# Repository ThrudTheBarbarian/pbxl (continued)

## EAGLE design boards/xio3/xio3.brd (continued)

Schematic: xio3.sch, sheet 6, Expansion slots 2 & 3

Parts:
C55, C56: 0.1uF; C0201
LD_2P, LD_3P: SML-D12D1WT86; CHIPLED_0603
R63, R64: 10K; R0201
R101, R104: 59R; R0402
SLOT2, SLOT3: PCIE_64; PCI-E_64

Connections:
!LO_CCTL!: SLOT2.A27, SLOT3.A27; also elsewhere on the board
!LO_EXTSEL!: SLOT2.A29, SLOT3.A29; also elsewhere on the board
!LO_HALT!: SLOT2.B13, SLOT3.B13; also elsewhere on the board
!LO_IRQ!: SLOT2.B14, SLOT3.B14; also elsewhere on the board
!LO_MPD!: SLOT2.A30, SLOT3.A30; also elsewhere on the board
!LO_REF!: SLOT2.B15, SLOT3.B15; also elsewhere on the board
!LO_RST!: SLOT2.B16, SLOT3.B16; also elsewhere on the board
+3V3: SLOT2.A2, SLOT3.A2, SLOT3.A3; also elsewhere on the board
+5V: C55.1, C56.1, SLOT2.B1, SLOT2.B2, SLOT2.B3, SLOT3.B1, SLOT3.B2, SLOT3.B3; also elsewhere on the board
GND: C55.2, C56.2, LD_2P.C, LD_3P.C, R63.1, R64.1, SLOT2.A1, SLOT2.A3, SLOT2.A4, SLOT2.A5, SLOT2.B32, SLOT3.A1, SLOT3.A4, SLOT3.A5, SLOT3.B32; also elsewhere on the board
HBUS0: SLOT2.B18, SLOT3.B18; also elsewhere on the board
HBUS1: SLOT2.B19, SLOT3.B19; also elsewhere on the board
HBUS2: SLOT2.B20, SLOT3.B20; also elsewhere on the board
HBUS3: SLOT2.B21, SLOT3.B21; also elsewhere on the board
HBUS4: SLOT2.B22, SLOT3.B22; also elsewhere on the board
HBUS5: SLOT2.B23, SLOT3.B23; also elsewhere on the board
HBUS6: SLOT2.B24, SLOT3.B24; also elsewhere on the board
HBUS7: SLOT2.B25, SLOT3.B25; also elsewhere on the board
HBUS8: SLOT2.B26, SLOT3.B26; also elsewhere on the board
HBUS9: SLOT2.B27, SLOT3.B27; also elsewhere on the board
HBUS10: SLOT2.B28, SLOT3.B28; also elsewhere on the board
HBUS11: SLOT2.B29, SLOT3.B29; also elsewhere on the board
HBUS12: SLOT2.B30, SLOT3.B30; also elsewhere on the board
HBUS13: SLOT2.B31, SLOT3.B31; also elsewhere on the board
LO_A0: SLOT2.A11, SLOT3.A11; also elsewhere on the board
LO_A1: SLOT2.A12, SLOT3.A12; also elsewhere on the board
LO_A2: SLOT2.A13, SLOT3.A13; also elsewhere on the board
LO_A3: SLOT2.A14, SLOT3.A14; also elsewhere on the board
LO_A4: SLOT2.A15, SLOT3.A15; also elsewhere on the board
LO_A5: SLOT2.A16, SLOT3.A16; also elsewhere on the board
LO_A6: SLOT2.A17, SLOT3.A17; also elsewhere on the board
LO_A7: SLOT2.A18, SLOT3.A18; also elsewhere on the board
LO_A8: SLOT2.A19, SLOT3.A19; also elsewhere on the board
LO_A9: SLOT2.A20, SLOT3.A20; also elsewhere on the board
LO_A10: SLOT2.A21, SLOT3.A21; also elsewhere on the board
LO_A11: SLOT2.A22, SLOT3.A22; also elsewhere on the board
LO_A12: SLOT2.A23, SLOT3.A23; also elsewhere on the board
LO_A13: SLOT2.A24, SLOT3.A24; also elsewhere on the board
LO_A14: SLOT2.A25, SLOT3.A25; also elsewhere on the board
LO_A15: SLOT2.A26, SLOT3.A26; also elsewhere on the board
LO_CLK: SLOT2.A28, SLOT3.A28; also elsewhere on the board
LO_D0: SLOT2.B5, SLOT3.B5; also elsewhere on the board
LO_D1: SLOT2.B6, SLOT3.B6; also elsewhere on the board
LO_D2: SLOT2.B7, SLOT3.B7; also elsewhere on the board
LO_D3: SLOT2.B8, SLOT3.B8; also elsewhere on the board
LO_D4: SLOT2.B9, SLOT3.B9; also elsewhere on the board
LO_D5: SLOT2.B10, SLOT3.B10; also elsewhere on the board
LO_D6: SLOT2.B11, SLOT3.B11; also elsewhere on the board
LO_D7: SLOT2.B12, SLOT3.B12; also elsewhere on the board
LO_R/!W!: SLOT2.B17, SLOT3.B17; also elsewhere on the board
LO_RD4: SLOT2.A31, SLOT3.A31; also elsewhere on the board
LO_RD5: SLOT2.A32, SLOT3.A32; also elsewhere on the board
unnamed: LD_2P.A, R101.2
unnamed: LD_3P.A, R104.2
S2_PRESENT: R63.2, R101.1, SLOT2.B4
S3_PRESENT: R64.2, R104.1, SLOT3.B4
SPI2_IRQ: SLOT2.A8; also elsewhere on the board
SPI2_MISO: SLOT2.A10; also elsewhere on the board
SPI2_MOSI: SLOT2.A9; also elsewhere on the board
SPI3_IRQ: SLOT3.A8; also elsewhere on the board
SPI3_MISO: SLOT3.A10; also elsewhere on the board
SPI3_MOSI: SLOT3.A9; also elsewhere on the board
VALID_RD: SLOT2.A7, SLOT3.A7; also elsewhere on the board
VALID_WR: SLOT2.A6, SLOT3.A6; also elsewhere on the board

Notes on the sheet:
Slots 2,3
Slot id: 0,1,0
Slot id: 0,1,1
B1,2,3 B4 A1,2,3 A4,5,6,7
+5V Card-present Slot ID GND
Orange LED

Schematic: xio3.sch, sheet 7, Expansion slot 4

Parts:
C81: 0.1uF; C0201
LD_4P: SML-D12D1WT86; CHIPLED_0603
R65: 10K; R0201
R107: 59R; R0402
SLOT4: PCIE_64; PCI-E_64

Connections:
!LO_CCTL!: SLOT4.A27; also elsewhere on the board
!LO_EXTSEL!: SLOT4.A29; also elsewhere on the board
!LO_HALT!: SLOT4.B13; also elsewhere on the board
!LO_IRQ!: SLOT4.B14; also elsewhere on the board
!LO_MPD!: SLOT4.A30; also elsewhere on the board
!LO_REF!: SLOT4.B15; also elsewhere on the board
!LO_RST!: SLOT4.B16; also elsewhere on the board
+3V3: SLOT4.A1; also elsewhere on the board
+5V: C81.1, SLOT4.B1, SLOT4.B2, SLOT4.B3; also elsewhere on the board
GND: C81.2, LD_4P.C, R65.1, SLOT4.A2, SLOT4.A3, SLOT4.A4, SLOT4.A5, SLOT4.B32; also elsewhere on the board
HBUS0: SLOT4.B18; also elsewhere on the board
HBUS1: SLOT4.B19; also elsewhere on the board
HBUS2: SLOT4.B20; also elsewhere on the board
HBUS3: SLOT4.B21; also elsewhere on the board
HBUS4: SLOT4.B22; also elsewhere on the board
HBUS5: SLOT4.B23; also elsewhere on the board
HBUS6: SLOT4.B24; also elsewhere on the board
HBUS7: SLOT4.B25; also elsewhere on the board
HBUS8: SLOT4.B26; also elsewhere on the board
HBUS9: SLOT4.B27; also elsewhere on the board
HBUS10: SLOT4.B28; also elsewhere on the board
HBUS11: SLOT4.B29; also elsewhere on the board
HBUS12: SLOT4.B30; also elsewhere on the board
HBUS13: SLOT4.B31; also elsewhere on the board
LO_A0: SLOT4.A11; also elsewhere on the board
LO_A1: SLOT4.A12; also elsewhere on the board
LO_A2: SLOT4.A13; also elsewhere on the board
LO_A3: SLOT4.A14; also elsewhere on the board
LO_A4: SLOT4.A15; also elsewhere on the board
LO_A5: SLOT4.A16; also elsewhere on the board
LO_A6: SLOT4.A17; also elsewhere on the board
LO_A7: SLOT4.A18; also elsewhere on the board
LO_A8: SLOT4.A19; also elsewhere on the board
LO_A9: SLOT4.A20; also elsewhere on the board
LO_A10: SLOT4.A21; also elsewhere on the board
LO_A11: SLOT4.A22; also elsewhere on the board
LO_A12: SLOT4.A23; also elsewhere on the board
LO_A13: SLOT4.A24; also elsewhere on the board
LO_A14: SLOT4.A25; also elsewhere on the board
LO_A15: SLOT4.A26; also elsewhere on the board
LO_CLK: SLOT4.A28; also elsewhere on the board
LO_D0: SLOT4.B5; also elsewhere on the board
LO_D1: SLOT4.B6; also elsewhere on the board
LO_D2: SLOT4.B7; also elsewhere on the board
LO_D3: SLOT4.B8; also elsewhere on the board
LO_D4: SLOT4.B9; also elsewhere on the board
LO_D5: SLOT4.B10; also elsewhere on the board
LO_D6: SLOT4.B11; also elsewhere on the board
LO_D7: SLOT4.B12; also elsewhere on the board
LO_R/!W!: SLOT4.B17; also elsewhere on the board
LO_RD4: SLOT4.A31; also elsewhere on the board
LO_RD5: SLOT4.A32; also elsewhere on the board
unnamed: LD_4P.A, R107.2
S4_PRESENT: R65.2, R107.1, SLOT4.B4
SPI4_IRQ: SLOT4.A8; also elsewhere on the board
SPI4_MISO: SLOT4.A10; also elsewhere on the board
SPI4_MOSI: SLOT4.A9; also elsewhere on the board
VALID_RD: SLOT4.A7; also elsewhere on the board
VALID_WR: SLOT4.A6; also elsewhere on the board

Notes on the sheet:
Slot 4
B1,2,3 B5,6,7 B4 A1,2,3 A4,5,6,7
+5V Slot 3.3v Card-present Slot ID GND
Orange LED

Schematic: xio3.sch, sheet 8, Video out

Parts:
JP2: PINHD-2X10; 2X10
R28, R29: 100R; R0201
RN1, RN5, RN8: 1K; ACAS0612
RN2, RN3, RN4, RN6, RN7, RN9, RN10, RN11: 2K; ACAS0612
U$2: DB15

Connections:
+5V: JP2.2; also elsewhere on the board
GND: JP2.20, U$2.5, U$2.6, U$2.7, U$2.8, U$2.10; also elsewhere on the board
unnamed: RN4.2A (1), RN4.3A (1)
unnamed: RN2.3B (2), RN2.4B (2)
unnamed: RN3.1B (2), RN3.2B (2)
unnamed: RN3.2A (1), RN3.3A (1)
unnamed: RN3.3B (2), RN3.4B (2)
unnamed: RN6.3B (2), RN6.4B (2)
unnamed: RN7.1B (2), RN7.2B (2)
unnamed: RN7.2A (1), RN7.3A (1)
unnamed: RN7.3B (2), RN7.4B (2)
unnamed: RN4.1B (2), RN4.2B (2)
unnamed: RN4.3B (2), RN4.4B (2)
unnamed: RN4.4A (1), RN11.1A (1)
unnamed: RN11.1B (2), RN11.2B (2)
unnamed: RN11.2A (1), RN11.3A (1)
unnamed: RN11.3B (2), RN11.4B (2)
unnamed: RN9.3B (2), RN9.4B (2)
unnamed: RN10.1B (2), RN10.2B (2)
unnamed: RN10.2A (1), RN10.3A (1)
unnamed: RN10.3B (2), RN10.4B (2)
VGA_B0: JP2.1, RN10.1A (1); also elsewhere on the board
VGA_B1: JP2.3, RN9.3A (1); also elsewhere on the board
VGA_B2: JP2.5, RN9.1A (1); also elsewhere on the board
VGA_B3: JP2.7, RN8.4A (1); also elsewhere on the board
VGA_B4: JP2.9, RN8.1A (1), RN8.2A (1); also elsewhere on the board
VGA_BLU: RN8.1B (2), RN8.2B (2), RN8.4B (2), RN9.1B (2), RN9.4A (1), RN10.4A (1), U$2.3
VGA_G0: JP2.4, RN4.1A (1); also elsewhere on the board
VGA_G1: JP2.6, RN7.1A (1); also elsewhere on the board
VGA_G2: JP2.8, RN6.3A (1); also elsewhere on the board
VGA_G3: JP2.10, RN6.1A (1); also elsewhere on the board
VGA_G4: JP2.12, RN5.4A (1); also elsewhere on the board
VGA_G5: JP2.14, RN5.1A (1), RN5.2A (1); also elsewhere on the board
VGA_GRN: RN5.1B (2), RN5.2B (2), RN5.4B (2), RN6.1B (2), RN6.4A (1), RN7.4A (1), RN11.4A (1), U$2.2
VGA_HS: R29.1, U$2.13
VGA_HSYNC: JP2.16, R29.2; also elsewhere on the board
VGA_R0: JP2.11, RN3.1A (1); also elsewhere on the board
VGA_R1: JP2.13, RN2.3A (1); also elsewhere on the board
VGA_R2: JP2.15, RN2.1A (1); also elsewhere on the board
VGA_R3: JP2.17, RN1.4A (1); also elsewhere on the board
VGA_R4: JP2.19, RN1.1A (1), RN1.2A (1); also elsewhere on the board
VGA_RED: RN1.1B (2), RN1.2B (2), RN1.4B (2), RN2.1B (2), RN2.4A (1), RN3.4A (1), U$2.1
VGA_VS: R28.1, U$2.14
VGA_VSYNC: JP2.18, R28.2; also elsewhere on the board

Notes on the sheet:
Video Out

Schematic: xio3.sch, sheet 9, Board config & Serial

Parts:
ARCH_ID: 209-4MS; EDG-04
C89, C90, C91, C92, C94: 0.1uF; C0201
MEM_ID: 209-2MS; EDG-02
PID: 209-3MS; EDG-03
R6, R7, R8, R9, R14, R15, R16, R17, R18: 47K; R0201
R11, R12, R122, R123, R124: 1K; R0201
SERIAL0: 9-way D; DB9
SERIAL_BUF0: MAX3232ECDR; SO16

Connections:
+3V3: C94.2, R11.1, R12.1, R122.1, R123.1, R124.1, SERIAL_BUF0.16 (VCC); also elsewhere on the board
ARCH0: ARCH_ID.1, R9.1
ARCH1: ARCH_ID.2, R8.1
ARCH2: ARCH_ID.3, R7.1
ARCH3: ARCH_ID.4, R6.1
CTS1: SERIAL0.7, SERIAL_BUF0.8 (R2IN)
GND: C91.2, C92.2, C94.1, R6.2, R7.2, R8.2, R9.2, R14.2, R15.2, R16.2, R17.2, R18.2, SERIAL0.5, SERIAL_BUF0.15 (GND); also elsewhere on the board
MCU_CTS: SERIAL_BUF0.9 (R2OUT); also elsewhere on the board
MCU_RTS: R12.2, SERIAL_BUF0.10 (T2IN); also elsewhere on the board
MCU_RX: SERIAL_BUF0.12 (R1OUT); also elsewhere on the board
MCU_TX: R11.2, SERIAL_BUF0.11 (T1IN); also elsewhere on the board
MEM0: MEM_ID.1, R18.1
MEM1: MEM_ID.2, R17.1
unnamed: ARCH_ID.5, ARCH_ID.6, ARCH_ID.7, ARCH_ID.8, R122.2
unnamed: C89.2, SERIAL_BUF0.1 (C1+)
unnamed: C89.1, SERIAL_BUF0.3 (C1-)
unnamed: C90.2, SERIAL_BUF0.4 (C2+)
unnamed: C90.1, SERIAL_BUF0.5 (C2-)
unnamed: C91.1, SERIAL_BUF0.6 (V-)
unnamed: C92.1, SERIAL_BUF0.2 (V+)
unnamed: MEM_ID.3, MEM_ID.4, R123.2
unnamed: PID.4, PID.5, PID.6, R124.2
PID0: PID.1, R16.1
PID1: PID.2, R15.1
PID2: PID.3, R14.1
RTS1: SERIAL0.8, SERIAL_BUF0.7 (T2OUT)
RX1: SERIAL0.3, SERIAL_BUF0.13 (R1IN)
TX1: SERIAL0.2, SERIAL_BUF0.14 (T1OUT)

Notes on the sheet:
Architecture selection
Peripheral-ID selection
Memory-emulation selection
Serial & Config
Board Config
2-way and 4-way DIPs not at Seeed
For Vcc=3.3v, all caps are 0.1uF (See Table 2, pg 9 in datasheet)
the 'E' designation on the MAX3232 indicates that it has ESD protection built in
Serial I/O

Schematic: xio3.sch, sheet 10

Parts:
C41: 22uF; C0805
C42: 1uF; C0201
C43: 10uF; C0402K
C134: 0.1uF; C0201
R36, R37, R38, R39, R40, R41: 4K7; R0402
SD_SLOT: 5025700893

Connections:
+3V3: C41.1, C42.1, C43.1, C134.2, R36.2, R37.2, R38.2, R39.2, R40.2, R41.2, SD_SLOT.P$4 (VDD); also elsewhere on the board
GND: C41.2, C42.2, C43.2, C134.1, SD_SLOT.GND0 (SH1), SD_SLOT.GND1 (SH2), SD_SLOT.GND2 (SH3), SD_SLOT.GND3 (SH4), SD_SLOT.GND4 (SH5), SD_SLOT.P$6 (VSS); also elsewhere on the board
SD0: R36.1, SD_SLOT.P$7 (DAT0); also elsewhere on the board
SD1: R37.1, SD_SLOT.P$8 (DAT1); also elsewhere on the board
SD2: R38.1, SD_SLOT.P$1 (DAT2); also elsewhere on the board
SD3: R39.1, SD_SLOT.P$2 (DAT3); also elsewhere on the board
SDCD: R41.1, SD_SLOT.DTCT (CD); also elsewhere on the board
SDCLK: SD_SLOT.P$5 (CLK); also elsewhere on the board
SDCMD: R40.1, SD_SLOT.P$3 (CMD); also elsewhere on the board

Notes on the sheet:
Place pull-ups close to card socket
SD Card

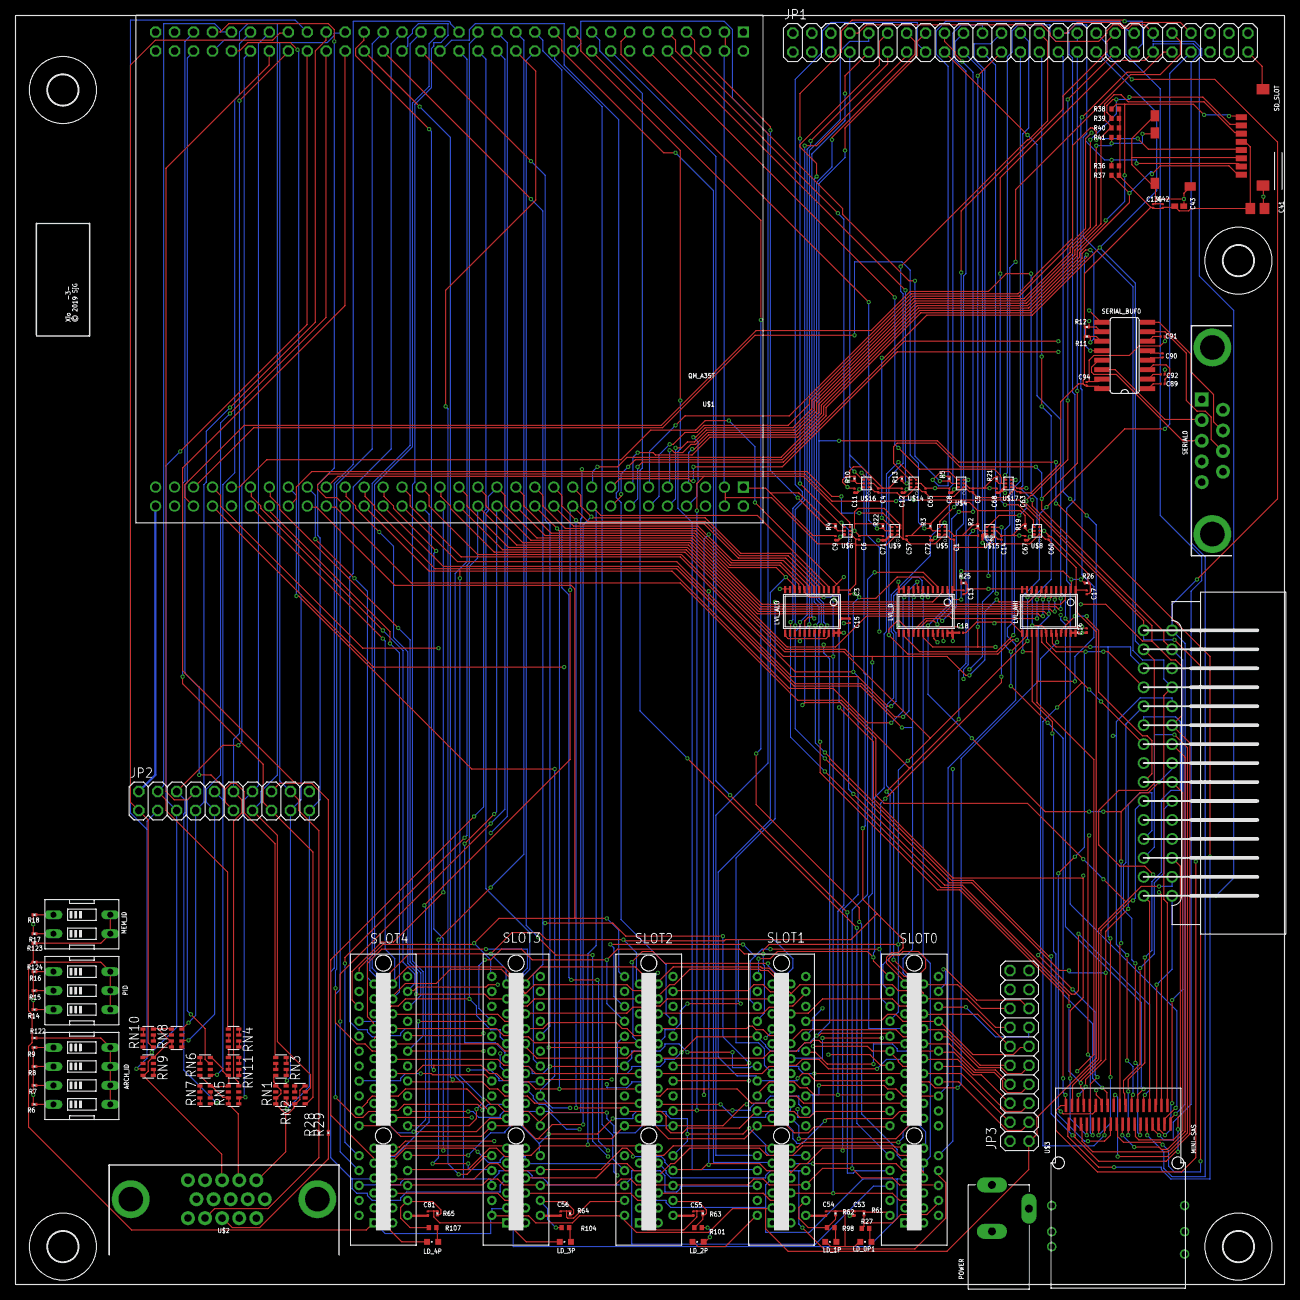
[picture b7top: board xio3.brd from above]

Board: 4 copper layers, 170.0 x 170.0 mm, 132 parts (0 on the bottom side), 201 nets.

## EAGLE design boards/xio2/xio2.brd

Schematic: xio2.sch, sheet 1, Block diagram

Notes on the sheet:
USB-C
STM32H743 (XIO) (TFBGA 240+25)
SPI4
@100 MHz
Slots 0..4
Bus Signals. Generate !D1xx!, !CCTL!, !S4!, !S5! from address. Total is 38 signals
RS232
32 MB SDRAM
/41
(32 bit)
POWER SW
USB Full-speed
CURRENT_OVER
VBUS_ENABLE
SD Card
@48
@400
NCP380
(OTG mode)
USB 'A'
DB9
5v supply @ 10A - Total power supply is 50W 3.3v from 5V, max power provided= 10A 3.3v main-board current sinks (max, in mA)
'XIO' STM32H7 IS66WV51216EBLL MAX3232 LEDs x6 NCP380 FPGA Slots Total
750 25 2 20 1 2000 5000 7798
0.5 mm core
0.12mm pre-preg
0.035mm
0.017mm
Layer stack-up
GND
Power
Dielectric constant: 4.2
Cycle time = 558ns
Valid address
Write
Read
177ns
422ns
486ns
225ns

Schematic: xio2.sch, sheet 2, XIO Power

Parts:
C1, C34: 10uF; C0402K
C2, C3, C4, C5, C6, C7, C8, C9, C10, C13, C16, C26, C27, C28, C29, C31, C32, C33, C98: 0.1uF; C0201
C14, C15: 16pF; C0201
C17, C18, C99: 2.2uF; C0201
H1, H2, H4, H5: MOUNT-HOLE3.2; 3,2
POWER: dc5vin; DCJ3P-14.2X11.0X9.0MM
R1, R5, R53, R72: 0R; R0201
R21: 33R; R0201
R88, R89, R90: 10K; R0201
XIO: STM32H743-XIO; BGA289C80P17X17_1400X1400X110
XIO-SWD: XIO_JTAG; SWD_DEBUG
Y2: FA-238 25.0000MB-K3; CRYSTAL_3.2X2.5

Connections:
!RESET!: C98.1, R89.2, XIO.K1 (!RST!), XIO-SWD.P10 (RESET); also elsewhere on the board
+3V3: C2.1, C3.1, C4.1, C5.1, C6.1, C7.1, C8.1, C9.1, C10.1, C16.1, C26.1, C27.1, C28.1, C29.1, C31.1, C32.1, C33.1, C34.1, R5.1, R21.2, R53.1, R88.1, R89.1, R90.1, XIO.A6 (VDDLDO), XIO.B1 (VBAT), XIO.C17 (VDDLDO), XIO.E6 (VDD), XIO.E9 (VDD), XIO.E11 (VDD), XIO.F5 (VDD), XIO.F17 (VDD33USB), XIO.G5 (VDD), XIO.G13 (VDD), XIO.H5 (VDD), XIO.H13 (VDD), XIO.J13 (VDD), XIO.K5 (VDD), XIO.K13 (VDD), XIO.L5 (VDD), XIO.L13 (VDD), XIO.M5 (VDD), XIO.M13 (VDD), XIO.N7 (VDD), XIO.N8 (VDD), XIO.N10 (VDD), XIO.N11 (VDD), XIO.N12 (VDD), XIO.P17 (VDD), XIO.U12 (VDDLDO), XIO-SWD.P1 (VDD_OUT); also elsewhere on the board
+5V: POWER.+; also elsewhere on the board
AGND: C1.2, C13.2, R72.2, XIO.N1 (VREF-), XIO.P1 (VSSA)
BOOT0: R1.1, R5.2, XIO.E8 (BOOT0)
GND: C2.2, C3.2, C4.2, C5.2, C6.2, C7.2, C8.2, C9.2, C10.2, C14.2, C15.2, C16.2, C17.2, C18.2, C26.2, C27.2, C28.2, C29.2, C31.2, C32.2, C33.2, C34.2, C98.2, C99.2, POWER.-1 (-), R1.2, R72.1, XIO.A1 (VSS), XIO.A17 (VSS), XIO.B2 (VSS), XIO.B6 (VSS), XIO.C10 (VSS), XIO.C13 (VSS), XIO.C16 (VSS), XIO.G7 (VSS), XIO.G8 (VSS), XIO.G9 (VSS), XIO.G10 (VSS), XIO.G11 (VSS), XIO.G16 (VSS), XIO.H7 (VSS), XIO.H8 (VSS), XIO.H9 (VSS), XIO.H10 (VSS), XIO.H11 (VSS), XIO.J3 (VSS), XIO.J7 (VSS), XIO.J8 (VSS), XIO.J9 (VSS), XIO.J10 (VSS), XIO.J11 (VSS), XIO.J16 (VSS), XIO.J17 (VSS), XIO.K7 (VSS), XIO.K8 (VSS), XIO.K9 (VSS), XIO.K10 (VSS), XIO.K11 (VSS), XIO.K15 (VSS), XIO.L7 (VSS), XIO.L8 (VSS), XIO.L9 (VSS), XIO.L10 (VSS), XIO.L11 (VSS), XIO.L15 (VSS), XIO.M15 (VSS), XIO.N16 (VSS), XIO.R4 (VSS), XIO.R8 (VSS), XIO.T12 (VSS), XIO.U1 (VSS), XIO.U17 (VSS), XIO-SWD.P3 (GND), XIO-SWD.P5 (GND), XIO-SWD.P9 (GND); also elsewhere on the board
PDR_ON: R53.2, XIO.E7 (PDR_ON)
XIO_CLK_IN: C14.1, XIO.J1 (PH0), Y2.2
XIO_CLK_OUT: C15.1, XIO.J2 (PH1), Y2.1
XIO_RX: XIO.F13 (PC7), XIO-SWD.P8 (USART_RX)
XIO_SWDCLK: XIO.B14 (PA14), XIO-SWD.P4 (SWD_CLK)
XIO_SWDIO: R90.2, XIO.C15 (PA13), XIO-SWD.P2 (SWDIO)
XIO_TX: R88.2, XIO.F14 (PC6), XIO-SWD.P6 (USART_TX)
XIO_VCAP1: C18.1, XIO.U11 (VCAP1)
XIO_VCAP2: C17.1, XIO.D17 (VCAP2)
XIO_VCAP3: C99.1, XIO.A7 (VCAP3)
XIO_VDDA: C1.1, C13.1, R21.1, XIO.L1 (VDDA), XIO.M1 (VREF+)

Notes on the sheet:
Power entry
XIO POWER
Regulated 5v supply at 10A. (JYH05010000B) Partial power plane on layer 14
Caps placed close to VDDA pin
Caps placed close to VCAP pins
(Load Cap 10pF, stray Cap 2pF)
Pullups
Filter on VDDA
Pullups etc. in panel to left
C.res1 = C.res2 = 2(C.load - C.stray)
5v-in is ok to NC

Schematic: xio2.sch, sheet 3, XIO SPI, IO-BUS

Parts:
R26, R27, R91, R92, R93: 33R; R0201
SPI_DBG: PINHD-1X5; 1X05
XIO: STM32H743-XIO; BGA289C80P17X17_1400X1400X110
XSPI5_DBG, XSPI6_DBG: PINHD-1X3; 1X03

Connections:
!ADDR_VALID_READ!: XIO.M2 (PC1); also elsewhere on the board
!ADDR_VALID_WRITE!: XIO.M3 (PC2); also elsewhere on the board
!IO_EXP_IRQ!: XIO.D3 (PE3); also elsewhere on the board
!IO_EXP_SEL!: XIO.N2 (PH2); also elsewhere on the board
!SPI_IRQ!: XIO.D2 (PE4); also elsewhere on the board
HOST_A0: XIO.U5 (PB0); also elsewhere on the board
HOST_A1: XIO.T5 (PB1); also elsewhere on the board
HOST_A2: XIO.R6 (PB2); also elsewhere on the board
HOST_A3: XIO.C6 (PB3); also elsewhere on the board
HOST_A4: XIO.B7 (PB4); also elsewhere on the board
HOST_A5: XIO.A5 (PB5); also elsewhere on the board
HOST_A6: XIO.B5 (PB6); also elsewhere on the board
HOST_A7: XIO.C5 (PB7); also elsewhere on the board
HOST_A8: XIO.D5 (PB8); also elsewhere on the board
HOST_A9: XIO.D4 (PB9); also elsewhere on the board
HOST_A10: XIO.P11 (PB10); also elsewhere on the board
HOST_A11: XIO.P12 (PB11); also elsewhere on the board
HOST_A12: XIO.T14 (PB12); also elsewhere on the board
HOST_A13: XIO.U14 (PB13); also elsewhere on the board
HOST_A14: XIO.U15 (PB14); also elsewhere on the board
HOST_A15: XIO.T15 (PB15); also elsewhere on the board
unnamed: R26.2, XIO.C3 (PE2)
unnamed: R27.2, XIO.E5 (PE6)
SPI_CLK: R26.1, SPI_DBG.1; also elsewhere on the board
SPI_IRQ0: SPI_DBG.4, XIO.H15 (PG3); also elsewhere on the board
SPI_IRQ1: XIO.G15 (PG6); also elsewhere on the board
SPI_IRQ2: XIO.A10 (PG9); also elsewhere on the board
SPI_IRQ3: XIO.A9 (PG10); also elsewhere on the board
SPI_IRQ4: XIO.B9 (PG11); also elsewhere on the board
SPI_MISO: SPI_DBG.2, XIO.D1 (PE5); also elsewhere on the board
SPI_MOSI: R27.1, SPI_DBG.3; also elsewhere on the board
SPI_MUX_IN: XIO.P2 (PH3); also elsewhere on the board
SPI_SS0: SPI_DBG.5, XIO.L2 (PC0); also elsewhere on the board
SPI_SS1: XIO.T4 (PC4); also elsewhere on the board
SPI_SS2: XIO.U4 (PC5); also elsewhere on the board
SPI_SS3: XIO.C2 (PC14); also elsewhere on the board
SPI_SS4: XIO.C1 (PC15); also elsewhere on the board
STM_MUX_CTL: XIO.M4 (PC3); also elsewhere on the board
STM_MUX_D0: XIO.N5 (PA0); also elsewhere on the board
STM_MUX_D1: XIO.N4 (PA1); also elsewhere on the board
STM_MUX_D2: XIO.N3 (PA2); also elsewhere on the board
STM_MUX_D3: XIO.U2 (PA3); also elsewhere on the board
STM_MUX_D4: XIO.U3 (PA4); also elsewhere on the board
STM_MUX_D5: XIO.T3 (PA5); also elsewhere on the board
STM_MUX_D6: XIO.R3 (PA6); also elsewhere on the board
STM_MUX_D7: XIO.R5 (PA7); also elsewhere on the board
XSPI5_MISO: R91.2, XSPI5_DBG.2; also elsewhere on the board
XSPI5_MISO_R: R91.1, XIO.K4 (PF8)
XSPI5_MOSI: XIO.L4 (PF9), XSPI5_DBG.3; also elsewhere on the board
XSPI5_SCK: XIO.K3 (PF7), XSPI5_DBG.1; also elsewhere on the board
XSPI6_MISO: XIO.C9 (PG12), XSPI6_DBG.2; also elsewhere on the board
XSPI6_MOSI: R93.2, XSPI6_DBG.3; also elsewhere on the board
XSPI6_MOSI_R: R93.1, XIO.D8 (PG14)
XSPI6_SCK: R92.2, XSPI6_DBG.1; also elsewhere on the board
XSPI6_SCK_R: R92.1, XIO.D9 (PG13)

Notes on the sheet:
Slot SPI, @ 100MHz
XIO SPI, IOBUS
Add termination resistors close to source
SPI5 to be used with FPGA as master. SPI6 to be used with STM as master Resistors sited close to source signal
FPGA SPI, @ 100MHz
FPGA to STM32 Host interface
SPI termination
FPGA decodes bus and handles timings. Sends IRQ when bus is valid to read/write

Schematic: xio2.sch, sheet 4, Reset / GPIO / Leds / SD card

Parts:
C41: 22uF; C0805
C42: 1uF; C0201
C43: 10uF; C0402K
C134, C137: 0.1uF; C0201
C135: 120pF; C0201
C136: 0.01uF; C0201
DBG0, DBG1, DBG2: YELLOW_LED; CHIPLED_0603
R2, R3, R4: 130R; R0402
R36, R37, R38, R39, R40, R41: 47K; R0402
RESET_XIO: TAC_SWITCH; TACTILE-PTH
SD_SLOT: 5025700893
VREG_MON: TPS3808G33DBVR; SOT23-6
XIO: STM32H743-XIO; BGA289C80P17X17_1400X1400X110

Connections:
!MR!: C136.1, RESET_XIO.1, RESET_XIO.2, VREG_MON.3 (!MR!)
!RESET!: VREG_MON.1 (!RESET!); also elsewhere on the board
+3V3: C41.1, C42.1, C43.1, C134.2, C137.1, R2.1, R3.1, R4.1, R36.2, R37.2, R38.2, R39.2, R40.2, R41.2, SD_SLOT.P$4 (VDD), VREG_MON.5 (SENSE), VREG_MON.6 (VDD); also elsewhere on the board
GND: C41.2, C42.2, C43.2, C134.1, C135.2, C136.2, C137.2, RESET_XIO.3, RESET_XIO.4, SD_SLOT.GND0 (SH1), SD_SLOT.GND1 (SH2), SD_SLOT.GND2 (SH3), SD_SLOT.GND3 (SH4), SD_SLOT.GND4 (SH5), SD_SLOT.P$6 (VSS), VREG_MON.2 (GND); also elsewhere on the board
unnamed: DBG0.A, R2.2
unnamed: DBG0.C, XIO.R15 (PD11)
unnamed: DBG1.C, XIO.R16 (PD12)
unnamed: DBG2.C, XIO.R17 (PD13)
unnamed: DBG1.A, R3.2
unnamed: DBG2.A, R4.2
unnamed: C135.1, VREG_MON.4 (CT)
SD0: R36.1, SD_SLOT.P$7 (DAT0), XIO.E13 (PC8)
SD1: R37.1, SD_SLOT.P$8 (DAT1), XIO.E14 (PC9)
SD2: R38.1, SD_SLOT.P$1 (DAT2), XIO.A13 (PC10)
SD3: R39.1, SD_SLOT.P$2 (DAT3), XIO.B13 (PC11)
SDCD: R41.1, SD_SLOT.DTCT (CD), XIO.E3 (PC13)
SDCLK: SD_SLOT.P$5 (CLK), XIO.C12
SDCMD: R40.1, SD_SLOT.P$3 (CMD), XIO.D12 (PD2)

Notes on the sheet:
Debug LEDs
Unused pins
Reset, LEDs, SD, unused
Reset monitor
!MR! has internal pull-up to VDD
SD Card
Place pull-ups close to card socket
Vf = 2.1v, current = 9mA using 130R

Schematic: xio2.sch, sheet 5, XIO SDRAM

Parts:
C19, C20, C21, C22, C23, C24, C167, C168, C169, C170, C171, C172: 0.1uF; C0201
C177: 4.7uF; C0201
R120, R121: 10K; R0201
SDRAM: IS42S32160F-7TLI; SOP50P1176X120-86
XIO: STM32H743-XIO; BGA289C80P17X17_1400X1400X110

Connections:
!SDRAM_CAS!: SDRAM.18 (!CAS!), XIO.D6 (PG15)
!SDRAM_RAS!: SDRAM.19 (!RAS!), XIO.T7 (PF11)
!SDRAM_WE!: SDRAM.17 (!WE!), XIO.P4 (PH5)
+3V3: C19.1, C20.1, C21.1, C22.1, C23.1, C24.1, C167.1, C168.1, C169.1, C170.1, C171.1, C172.1, C177.1, R121.1, SDRAM.1 (VDD), SDRAM.3 (VDDQ), SDRAM.9 (VDDQ), SDRAM.15 (VDD), SDRAM.29 (VDD), SDRAM.35 (VDDQ), SDRAM.41 (VDDQ), SDRAM.43 (VDD), SDRAM.49 (VDDQ), SDRAM.55 (VDDQ), SDRAM.75 (VDDQ), SDRAM.81 (VDDQ); also elsewhere on the board
GND: C19.2, C20.2, C21.2, C22.2, C23.2, C24.2, C167.2, C168.2, C169.2, C170.2, C171.2, C172.2, C177.2, R120.2, SDRAM.6 (VSSQ), SDRAM.12 (VSSQ), SDRAM.32 (VSSQ), SDRAM.38 (VSSQ), SDRAM.44 (VSS), SDRAM.46 (VSSQ), SDRAM.52 (VSSQ), SDRAM.58 (VSS), SDRAM.72 (VSS), SDRAM.78 (VSSQ), SDRAM.84 (VSSQ), SDRAM.86 (VSS); also elsewhere on the board
unnamed: R121.2, SDRAM.67 (CKE)
unnamed: R120.1, SDRAM.20 (!CS!)
SDRAM_A0: SDRAM.25 (A0), XIO.G4 (PF0)
SDRAM_A1: SDRAM.26 (A1), XIO.G3 (PF1)
SDRAM_A2: SDRAM.27 (A2), XIO.G1 (PF2)
SDRAM_A3: SDRAM.60 (A3), XIO.H4 (PF3)
SDRAM_A4: SDRAM.61 (A4), XIO.J5 (PF4)
SDRAM_A5: SDRAM.62 (A5), XIO.J4 (PF5)
SDRAM_A6: SDRAM.63 (A6), XIO.R7 (PF12)
SDRAM_A7: SDRAM.64 (A7), XIO.P7 (PF13)
SDRAM_A8: SDRAM.65 (A8), XIO.P8 (PF14)
SDRAM_A9: SDRAM.66 (A9), XIO.R9 (PF15)
SDRAM_A10: SDRAM.24 (A10), XIO.T8 (PG0)
SDRAM_A11: SDRAM.21 (A11), XIO.U8 (PG1)
SDRAM_A12: SDRAM.69 (A12), XIO.H16 (PG2)
SDRAM_BA0: SDRAM.22 (BA0), XIO.H14 (PG4)
SDRAM_BA1: SDRAM.23 (BA1), XIO.G14 (PG5)
SDRAM_CLK: SDRAM.68 (CLK), XIO.F15 (PG8)
SDRAM_D0: SDRAM.2 (DQ0), XIO.P16 (PD14)
SDRAM_D1: SDRAM.4 (DQ1), XIO.P15 (PD15)
SDRAM_D2: SDRAM.5 (DQ2), XIO.D13 (PD0)
SDRAM_D3: SDRAM.7 (DQ3), XIO.E12 (PD1)
SDRAM_D4: SDRAM.8 (DQ4), XIO.U9 (PE7)
SDRAM_D5: SDRAM.10 (DQ5), XIO.T9 (PE8)
SDRAM_D6: SDRAM.11 (DQ6), XIO.P9 (PE9)
SDRAM_D7: SDRAM.13 (DQ7), XIO.N9 (PE10)
SDRAM_D8: SDRAM.74 (DQ8), XIO.P10 (PE11)
SDRAM_D9: SDRAM.76 (DQ9), XIO.R10 (PE12)
SDRAM_D10: SDRAM.77 (DQ10), XIO.T10 (PE13)
SDRAM_D11: SDRAM.79 (DQ11), XIO.U10 (PE14)
SDRAM_D12: SDRAM.80 (DQ12), XIO.R11 (PE15)
SDRAM_D13: SDRAM.82 (DQ13), XIO.U16 (PD8)
SDRAM_D14: SDRAM.83 (DQ14), XIO.T17 (PD9)
SDRAM_D15: SDRAM.85 (DQ15), XIO.T16 (PD10)
SDRAM_D16: SDRAM.31 (DQ16), XIO.T13 (PH8)
SDRAM_D17: SDRAM.33 (DQ17), XIO.R13 (PH9)
SDRAM_D18: SDRAM.34 (DQ18), XIO.P13 (PH10)
SDRAM_D19: SDRAM.36 (DQ19), XIO.P14 (PH11)
SDRAM_D20: SDRAM.37 (DQ20), XIO.R14 (PH12)
SDRAM_D21: SDRAM.39 (DQ21), XIO.D16 (PH13)
SDRAM_D22: SDRAM.40 (DQ22), XIO.B17 (PH14)
SDRAM_D23: SDRAM.42 (DQ23), XIO.B16 (PH15)
SDRAM_D24: SDRAM.45 (DQ24), XIO.A16 (PI0)
SDRAM_D25: SDRAM.47 (DQ25), XIO.A15 (PI1)
SDRAM_D26: SDRAM.48 (DQ26), XIO.B15 (PI2)
SDRAM_D27: SDRAM.50 (DQ27), XIO.C14 (PI3)
SDRAM_D28: SDRAM.51 (DQ28), XIO.A2 (PI6)
SDRAM_D29: SDRAM.53 (DQ29), XIO.B3 (PI7)
SDRAM_D30: SDRAM.54 (DQ30), XIO.E2 (PI9)
SDRAM_D31: SDRAM.56 (DQ31), XIO.F3 (PI10)
SDRAM_DQM0: SDRAM.16 (DQM0), XIO.C4 (PE0)
SDRAM_DQM1: SDRAM.71 (DQM1), XIO.B4 (PE1)
SDRAM_DQM2: SDRAM.28 (DQM2), XIO.A4 (PI4)
SDRAM_DQM3: SDRAM.59 (DQM3), XIO.A3 (PI5)

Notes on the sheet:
XIO SDRAM (32 bit)

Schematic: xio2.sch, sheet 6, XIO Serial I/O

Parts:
C89, C90, C91, C92, C94, C106: 0.1uF; C0201
IO_EXP: MCP23S17T-E/SS; SSOP28
R11, R12: 1K; R0201
SERIAL0: 9-way D; DB9
SERIAL_BUF0: MAX3232ECDR; SO16
XIO: STM32H743-XIO; BGA289C80P17X17_1400X1400X110

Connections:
!IO_EXP_IRQ!: IO_EXP.19 (INTB), IO_EXP.20 (INTA); also elsewhere on the board
!IO_EXP_SEL!: IO_EXP.11 (!CS!); also elsewhere on the board
!RESET!: IO_EXP.18 (!RESET!); also elsewhere on the board
+3V3: C94.2, C106.2, IO_EXP.9 (VDD), R11.1, R12.1, SERIAL_BUF0.16 (VCC); also elsewhere on the board
ARCH0: IO_EXP.1 (GPB0); also elsewhere on the board
ARCH1: IO_EXP.2 (GPB1); also elsewhere on the board
ARCH2: IO_EXP.3 (GPB2); also elsewhere on the board
ARCH3: IO_EXP.4 (GPB3); also elsewhere on the board
CTS1: SERIAL0.7, SERIAL_BUF0.8 (R2IN)
EXT_IO0: IO_EXP.7 (GPB6); also elsewhere on the board
EXT_IO1: IO_EXP.8 (GPB7); also elsewhere on the board
GND: C91.2, C92.2, C94.1, C106.1, IO_EXP.10 (VSS), IO_EXP.15 (A0), IO_EXP.16 (A1), IO_EXP.17 (A2), SERIAL0.5, SERIAL_BUF0.15 (GND); also elsewhere on the board
MCU_CTS: SERIAL_BUF0.9 (R2OUT), XIO.B12 (PD3)
MCU_RTS: R12.2, SERIAL_BUF0.10 (T2IN), XIO.A12 (PD4)
MCU_RX: SERIAL_BUF0.12 (R1OUT), XIO.B11 (PD6)
MCU_TX: R11.2, SERIAL_BUF0.11 (T1IN), XIO.A11 (PD5)
MEM0: IO_EXP.5 (GPB4); also elsewhere on the board
MEM1: IO_EXP.6 (GPB5); also elsewhere on the board
unnamed: C89.2, SERIAL_BUF0.1 (C1+)
unnamed: C89.1, SERIAL_BUF0.3 (C1-)
unnamed: C90.2, SERIAL_BUF0.4 (C2+)
unnamed: C90.1, SERIAL_BUF0.5 (C2-)
unnamed: C91.1, SERIAL_BUF0.6 (V-)
unnamed: C92.1, SERIAL_BUF0.2 (V+)
PID0: IO_EXP.26 (GPA5); also elsewhere on the board
PID1: IO_EXP.27 (GPA6); also elsewhere on the board
PID2: IO_EXP.28 (GPA7); also elsewhere on the board
RTS1: SERIAL0.8, SERIAL_BUF0.7 (T2OUT)
RX1: SERIAL0.3, SERIAL_BUF0.13 (R1IN)
S0_PRESENT: IO_EXP.21 (GPA0); also elsewhere on the board
S1_PRESENT: IO_EXP.22 (GPA1); also elsewhere on the board
S2_PRESENT: IO_EXP.23 (GPA2); also elsewhere on the board
S3_PRESENT: IO_EXP.24 (GPA3); also elsewhere on the board
S4_PRESENT: IO_EXP.25 (GPA4); also elsewhere on the board
SPI_CLK: IO_EXP.12 (SCK); also elsewhere on the board
SPI_MISO: IO_EXP.13 (MOSI); also elsewhere on the board
SPI_MOSI: IO_EXP.14 (MISO); also elsewhere on the board
TX1: SERIAL0.2, SERIAL_BUF0.14 (T1OUT)

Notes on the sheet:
Serial IO / Slot presence
For Vcc=3.3v, all caps are 0.1uF (See Table 2, pg 9 in datasheet)
the 'E' designation on the MAX3232 indicates that it has ESD protection built in
Serial I/O
Slot presence

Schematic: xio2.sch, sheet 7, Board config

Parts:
ARCH_ID: 209-4MS; EDG-04
C80, C87, C113, C114, C115, C116, C117, C118, C119, C120, C121, C122, C123, C124, C125, C126, C127, C128, C129, C130, C131, C132, C133, C138: 0.1uF; C0201
MEM_ID: 209-2MS; EDG-02
PID: 209-3MS; EDG-03
R6, R7, R8, R9, R14, R15, R16, R17, R18: 47K; R0201
R122, R123, R124: 1K; R0201
XIO: STM32H743-XIO; BGA289C80P17X17_1400X1400X110

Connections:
+3V3: C123.1, C124.1, C125.1, C126.1, C127.1, C128.1, C129.1, C130.1, C131.1, C132.1, C133.1, C138.1, R122.1, R123.1, R124.1; also elsewhere on the board
+5V: C80.1, C87.1, C113.1, C114.1, C115.1, C116.1, C117.1, C118.1, C119.1, C120.1, C121.1, C122.1; also elsewhere on the board
ARCH0: ARCH_ID.1, R9.1; also elsewhere on the board
ARCH1: ARCH_ID.2, R8.1; also elsewhere on the board
ARCH2: ARCH_ID.3, R7.1; also elsewhere on the board
ARCH3: ARCH_ID.4, R6.1; also elsewhere on the board
GND: C80.2, C87.2, C113.2, C114.2, C115.2, C116.2, C117.2, C118.2, C119.2, C120.2, C121.2, C122.2, C123.2, C124.2, C125.2, C126.2, C127.2, C128.2, C129.2, C130.2, C131.2, C132.2, C133.2, C138.2, R6.2, R7.2, R8.2, R9.2, R14.2, R15.2, R16.2, R17.2, R18.2, XIO.F1, XIO.F2, XIO.G2; also elsewhere on the board
MEM0: MEM_ID.1, R18.1; also elsewhere on the board
MEM1: MEM_ID.2, R17.1; also elsewhere on the board
unnamed: ARCH_ID.5, ARCH_ID.6, ARCH_ID.7, ARCH_ID.8, R122.2
unnamed: MEM_ID.3, MEM_ID.4, R123.2
unnamed: PID.4, PID.5, PID.6, R124.2
PID0: PID.1, R16.1; also elsewhere on the board
PID1: PID.2, R15.1; also elsewhere on the board
PID2: PID.3, R14.1; also elsewhere on the board

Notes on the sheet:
Architecture selection
Peripheral-ID selection
Memory-emulation selection
Board config
Board Config
NC Pins
Ground-loop caps
2-way and 4-way DIPs not at Seeed

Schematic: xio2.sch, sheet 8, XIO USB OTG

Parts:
C108: 4.7uF; C0402
C173: 1uF; C0201
PSW: NCP380; SOT23-6
R119: 100K; R0201
USB: MINI-USB-UX60-MB-5ST; UX60-MB-5ST
USB_ESD: PUSB2X4YH; SOT363
XIO: STM32H743-XIO; BGA289C80P17X17_1400X1400X110

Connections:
+5V: C173.1, PSW.1 (IN), R119.1; also elsewhere on the board
GND: C108.2, C173.2, PSW.2 (GND), USB.5, USB_ESD.2 (GND); also elsewhere on the board
unnamed: PSW.3 (EN), XIO.A14 (PA15)
unnamed: PSW.4 (!FLAG!), R119.2, XIO.C11 (PD7)
XIO_USB_ID: USB.4, USB_ESD.1 (ESD), XIO.D14 (PA10)
XIO_USB_N: USB.2, USB_ESD.3 (ESD), XIO.E17 (PA11)
XIO_USB_P: USB.3, USB_ESD.4 (ESD), XIO.E16 (PA12)
XIO_USB_VBUS: C108.1, PSW.6 (OUT), USB.1, USB_ESD.6 (ESD), XIO.D15 (PA9)

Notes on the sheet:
XIO USB OTG
Trace thickness Prepreg thickness Trace width Inter-trace spacing Prepreg dielectric Differential impedance
0.035 mm 0.12 mm 10 mil 7 mil 4.4 90.5 ohms
USB2 connections
Note: PUSB2X4YH isn't on Seeed's list Check host-only circuit will work
C108 will fail the BOM processing as being of different type than all the other 4.7uF caps. This is expected, since C108 is higher voltage-rated

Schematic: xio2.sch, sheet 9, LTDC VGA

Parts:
ADV7125: ADV7125; QFN50P700X700X100-49T495
C37, C44, C93: 0.01uF; C0201
C38, C39, C40, C45: 0.1uF; C0201
C46: 1uF; C0201
D1, D2: BAT54S; SOT23
Q1, Q2: BSS138; SOT23
R10: 560R; R0201
R13, R50, R51: 1K; R0201
R19, R20, R22: 75R; R0201
R23: 4.7K; R0201
R24: 0R; R0201
VGA: 15-way D; DB15
VREG_VGA: AD1580ARTZ; SOT23
XIO: STM32H743-XIO; BGA289C80P17X17_1400X1400X110

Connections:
+3V3: ADV7125.13 (VCC), ADV7125.29 (VCC), ADV7125.30 (VCC), C37.1, C38.1, C39.1, C40.1, C44.1, C45.1, C93.1, Q1.1 (G), Q2.1 (G), R13.2, R23.2; also elsewhere on the board
+5V: D1.2 (C2), D2.2 (C2), R50.1, R51.1; also elsewhere on the board
GND: ADV7125.1 (GND), ADV7125.2 (GND), ADV7125.14 (GND), ADV7125.15 (GND), ADV7125.25 (GND), ADV7125.26 (GND), ADV7125.27 (!IOB!), ADV7125.31 (!IOG!), ADV7125.33 (!IOR!), ADV7125.39 (GND), ADV7125.40 (GND), ADV7125.49 (GND), C37.2, C38.2, C39.2, C40.2, C44.2, C46.2, C93.2, D1.1 (A1), D2.1 (A1), R10.1, R19.2, R20.2, R22.2, R24.1, VGA.5, VGA.6, VGA.7, VGA.8, VGA.10, VREG_VGA.2 (V-); also elsewhere on the board
LCD_B0: ADV7125.16 (B0), XIO.D11 (PJ12)
LCD_B1: ADV7125.17 (B1), XIO.E10 (PJ13)
LCD_B2: ADV7125.18 (B2), XIO.D10 (PJ14)
LCD_B3: ADV7125.19 (B3), XIO.B10 (PJ15)
LCD_B4: ADV7125.20 (B4), XIO.C8 (PK3)
LCD_B5: ADV7125.21 (B5), XIO.B8 (PK4)
LCD_B6: ADV7125.22 (B6), XIO.A8 (PK5)
LCD_B7: ADV7125.23 (B7), XIO.C7 (PK6)
LCD_BLANK: ADV7125.11 (!BLANK!), XIO.D7 (PK7)
LCD_CLK: ADV7125.24 (CLOCK), XIO.F16 (PG7)
LCD_G0: ADV7125.3 (G0), XIO.N14 (PJ7)
LCD_G1: ADV7125.4 (G1), XIO.N13 (PJ8)
LCD_G2: ADV7125.5 (G2), XIO.M14 (PJ9)
LCD_G3: ADV7125.6 (G3), XIO.L14 (PJ10)
LCD_G4: ADV7125.7 (G4), XIO.K14 (PJ11)
LCD_G5: ADV7125.8 (G5), XIO.J14 (PK0)
LCD_G6: ADV7125.9 (G6), XIO.J15 (PK1)
LCD_G7: ADV7125.10 (G7), XIO.H17 (PK2)
LCD_HS: Q2.2 (S), XIO.H1 (PI12)
LCD_R0: ADV7125.41 (R0), XIO.P5 (PI15)
LCD_R1: ADV7125.42 (R1), XIO.N6 (PJ0)
LCD_R2: ADV7125.43 (R2), XIO.P6 (PJ1)
LCD_R3: ADV7125.44 (R3), XIO.T6 (PJ2)
LCD_R4: ADV7125.45 (R4), XIO.U6 (PJ3)
LCD_R5: ADV7125.46 (R5), XIO.U7 (PJ4)
LCD_R6: ADV7125.47 (R6), XIO.R12 (PJ5)
LCD_R7: ADV7125.48 (R7), XIO.N15 (PJ6)
LCD_VS: Q1.2 (S), XIO.H2 (PI13)
unnamed: ADV7125.36 (VREF), C46.1, R13.1, VREG_VGA.1 (V+)
unnamed: ADV7125.35 (COMP), C45.2
unnamed: ADV7125.38 (!PSAVE!), R23.1
unnamed: ADV7125.37 (RSET), R10.2
unnamed: ADV7125.12 (!SYNC!), R24.2
VGA_B: ADV7125.28 (IOB), R22.1, VGA.3
VGA_G: ADV7125.32 (IOG), R20.1, VGA.2
VGA_HS: D1.3 (C1A2), Q2.3 (D), R51.2, VGA.13
VGA_R: ADV7125.34 (IOR), R19.1, VGA.1
VGA_VS: D2.3 (C1A2), Q1.3 (D), R50.2, VGA.14

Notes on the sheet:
LCD to VGA

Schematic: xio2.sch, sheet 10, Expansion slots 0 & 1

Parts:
C53, C54: 0.1uF; C0201
R61, R62: 10K; R0201
SLOT0, SLOT1: PCIE_64; PCI-E_64

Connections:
+3V3: SLOT0.B5, SLOT0.B6, SLOT0.B7, SLOT1.A3, SLOT1.B5, SLOT1.B6, SLOT1.B7; also elsewhere on the board
+5V: C53.1, C54.1, SLOT0.B1, SLOT0.B2, SLOT0.B3, SLOT1.B1, SLOT1.B2, SLOT1.B3; also elsewhere on the board
GND: C53.2, C54.2, R61.1, R62.1, SLOT0.A1, SLOT0.A2, SLOT0.A3, SLOT0.A4, SLOT0.A5, SLOT0.A6, SLOT0.A7, SLOT1.A1, SLOT1.A2, SLOT1.A4, SLOT1.A5, SLOT1.A6, SLOT1.A7; also elsewhere on the board
HOST_!EXTSEL!: SLOT0.B26, SLOT1.B26; also elsewhere on the board
HOST_!HALT!: SLOT0.B27, SLOT1.B27; also elsewhere on the board
HOST_!IRQ!: SLOT0.B28, SLOT1.B28; also elsewhere on the board
HOST_!MPD!: SLOT0.B29, SLOT1.B29; also elsewhere on the board
HOST_!REF!: SLOT0.B30, SLOT1.B30; also elsewhere on the board
HOST_!RST!: SLOT0.B31, SLOT1.B31; also elsewhere on the board
HOST_A0: SLOT0.A8, SLOT1.A8; also elsewhere on the board
HOST_A1: SLOT0.A9, SLOT1.A9; also elsewhere on the board
HOST_A2: SLOT0.A10, SLOT1.A10; also elsewhere on the board
HOST_A3: SLOT0.A11, SLOT1.A11; also elsewhere on the board
HOST_A4: SLOT0.A12, SLOT1.A12; also elsewhere on the board
HOST_A5: SLOT0.A13, SLOT1.A13; also elsewhere on the board
HOST_A6: SLOT0.A14, SLOT1.A14; also elsewhere on the board
HOST_A7: SLOT0.A15, SLOT1.A15; also elsewhere on the board
HOST_A8: SLOT0.A16, SLOT1.A16; also elsewhere on the board
HOST_A9: SLOT0.A17, SLOT1.A17; also elsewhere on the board
HOST_A10: SLOT0.A18, SLOT1.A18; also elsewhere on the board
HOST_A11: SLOT0.A19, SLOT1.A19; also elsewhere on the board
HOST_A12: SLOT0.A20, SLOT1.A20; also elsewhere on the board
HOST_A13: SLOT0.A21, SLOT1.A21; also elsewhere on the board
HOST_A14: SLOT0.A22, SLOT1.A22; also elsewhere on the board
HOST_A15: SLOT0.A23, SLOT1.A23; also elsewhere on the board
HOST_CLK: SLOT0.A24, SLOT1.A24; also elsewhere on the board
HOST_D0: SLOT0.A25, SLOT1.A25; also elsewhere on the board
HOST_D1: SLOT0.A26, SLOT1.A26; also elsewhere on the board
HOST_D2: SLOT0.A27, SLOT1.A27; also elsewhere on the board
HOST_D3: SLOT0.A28, SLOT1.A28; also elsewhere on the board
HOST_D4: SLOT0.A29, SLOT1.A29; also elsewhere on the board
HOST_D5: SLOT0.A30, SLOT1.A30; also elsewhere on the board
HOST_D6: SLOT0.A31, SLOT1.A31; also elsewhere on the board
HOST_D7: SLOT0.A32, SLOT1.A32; also elsewhere on the board
HOST_R/!W!: SLOT0.B32, SLOT1.B32; also elsewhere on the board
S0_PRESENT: R61.2, SLOT0.B4; also elsewhere on the board
S1_PRESENT: R62.2, SLOT1.B4; also elsewhere on the board
SBUS12_CTL0: SLOT0.B8, SLOT1.B8
SBUS12_CTL1: SLOT0.B9, SLOT1.B9
SBUS12_CTL2: SLOT0.B10, SLOT1.B10
SBUS12_CTL3: SLOT0.B11, SLOT1.B11
SBUS12_CTL4: SLOT0.B12, SLOT1.B12
SBUS12_D0: SLOT0.B18, SLOT1.B18
SBUS12_D1: SLOT0.B19, SLOT1.B19
SBUS12_D2: SLOT0.B20, SLOT1.B20
SBUS12_D3: SLOT0.B21, SLOT1.B21
SBUS12_D4: SLOT0.B22, SLOT1.B22
SBUS12_D5: SLOT0.B23, SLOT1.B23
SBUS12_D6: SLOT0.B24, SLOT1.B24
SBUS12_D7: SLOT0.B25, SLOT1.B25
SPI_CLK: SLOT0.B17, SLOT1.B17; also elsewhere on the board
SPI_IRQ0: SLOT0.B14; also elsewhere on the board
SPI_IRQ1: SLOT1.B14; also elsewhere on the board
SPI_MISO: SLOT0.B16, SLOT1.B16; also elsewhere on the board
SPI_MOSI: SLOT0.B15, SLOT1.B15; also elsewhere on the board
SPI_SS0: SLOT0.B13; also elsewhere on the board
SPI_SS1: SLOT1.B13; also elsewhere on the board

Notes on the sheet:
Slots 0,1
Slot id: 0,0,0
Slot id: 0,0,1
B1,2,3 B5,6,7 B4 A1,2,3 A4,5,6,7
+5V Slot 3.3v Card-present Slot ID GND
